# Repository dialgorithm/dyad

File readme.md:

<h1 align="center">
  dyad
  <br>
</h1>

<h4 align="center">
    esp32 + rp2040 dev board that's rpi zero sized
</h4>

## it features

- **ESP32-WROOM-32E** as the main controller
- **RP2040** as the secondary controller
- **micro sd** support
- **flash memory** for rp2040
- **dual** usb c, one for each mcu

## design

### 3d

| front                             | back                       |
| --------------------------------- | -------------------------- |
|  |  |

### overview

| schematic                          | pcb                    |
| ---------------------------------- | ---------------------- |
|  |  |

### layered pcb routes

| top layer                        | first layer                   |
| -------------------------------- | ----------------------------- |
|  |  |

| second layer                        | bottom layer                  |
| ----------------------------------- | ----------------------------- |
|  |  |

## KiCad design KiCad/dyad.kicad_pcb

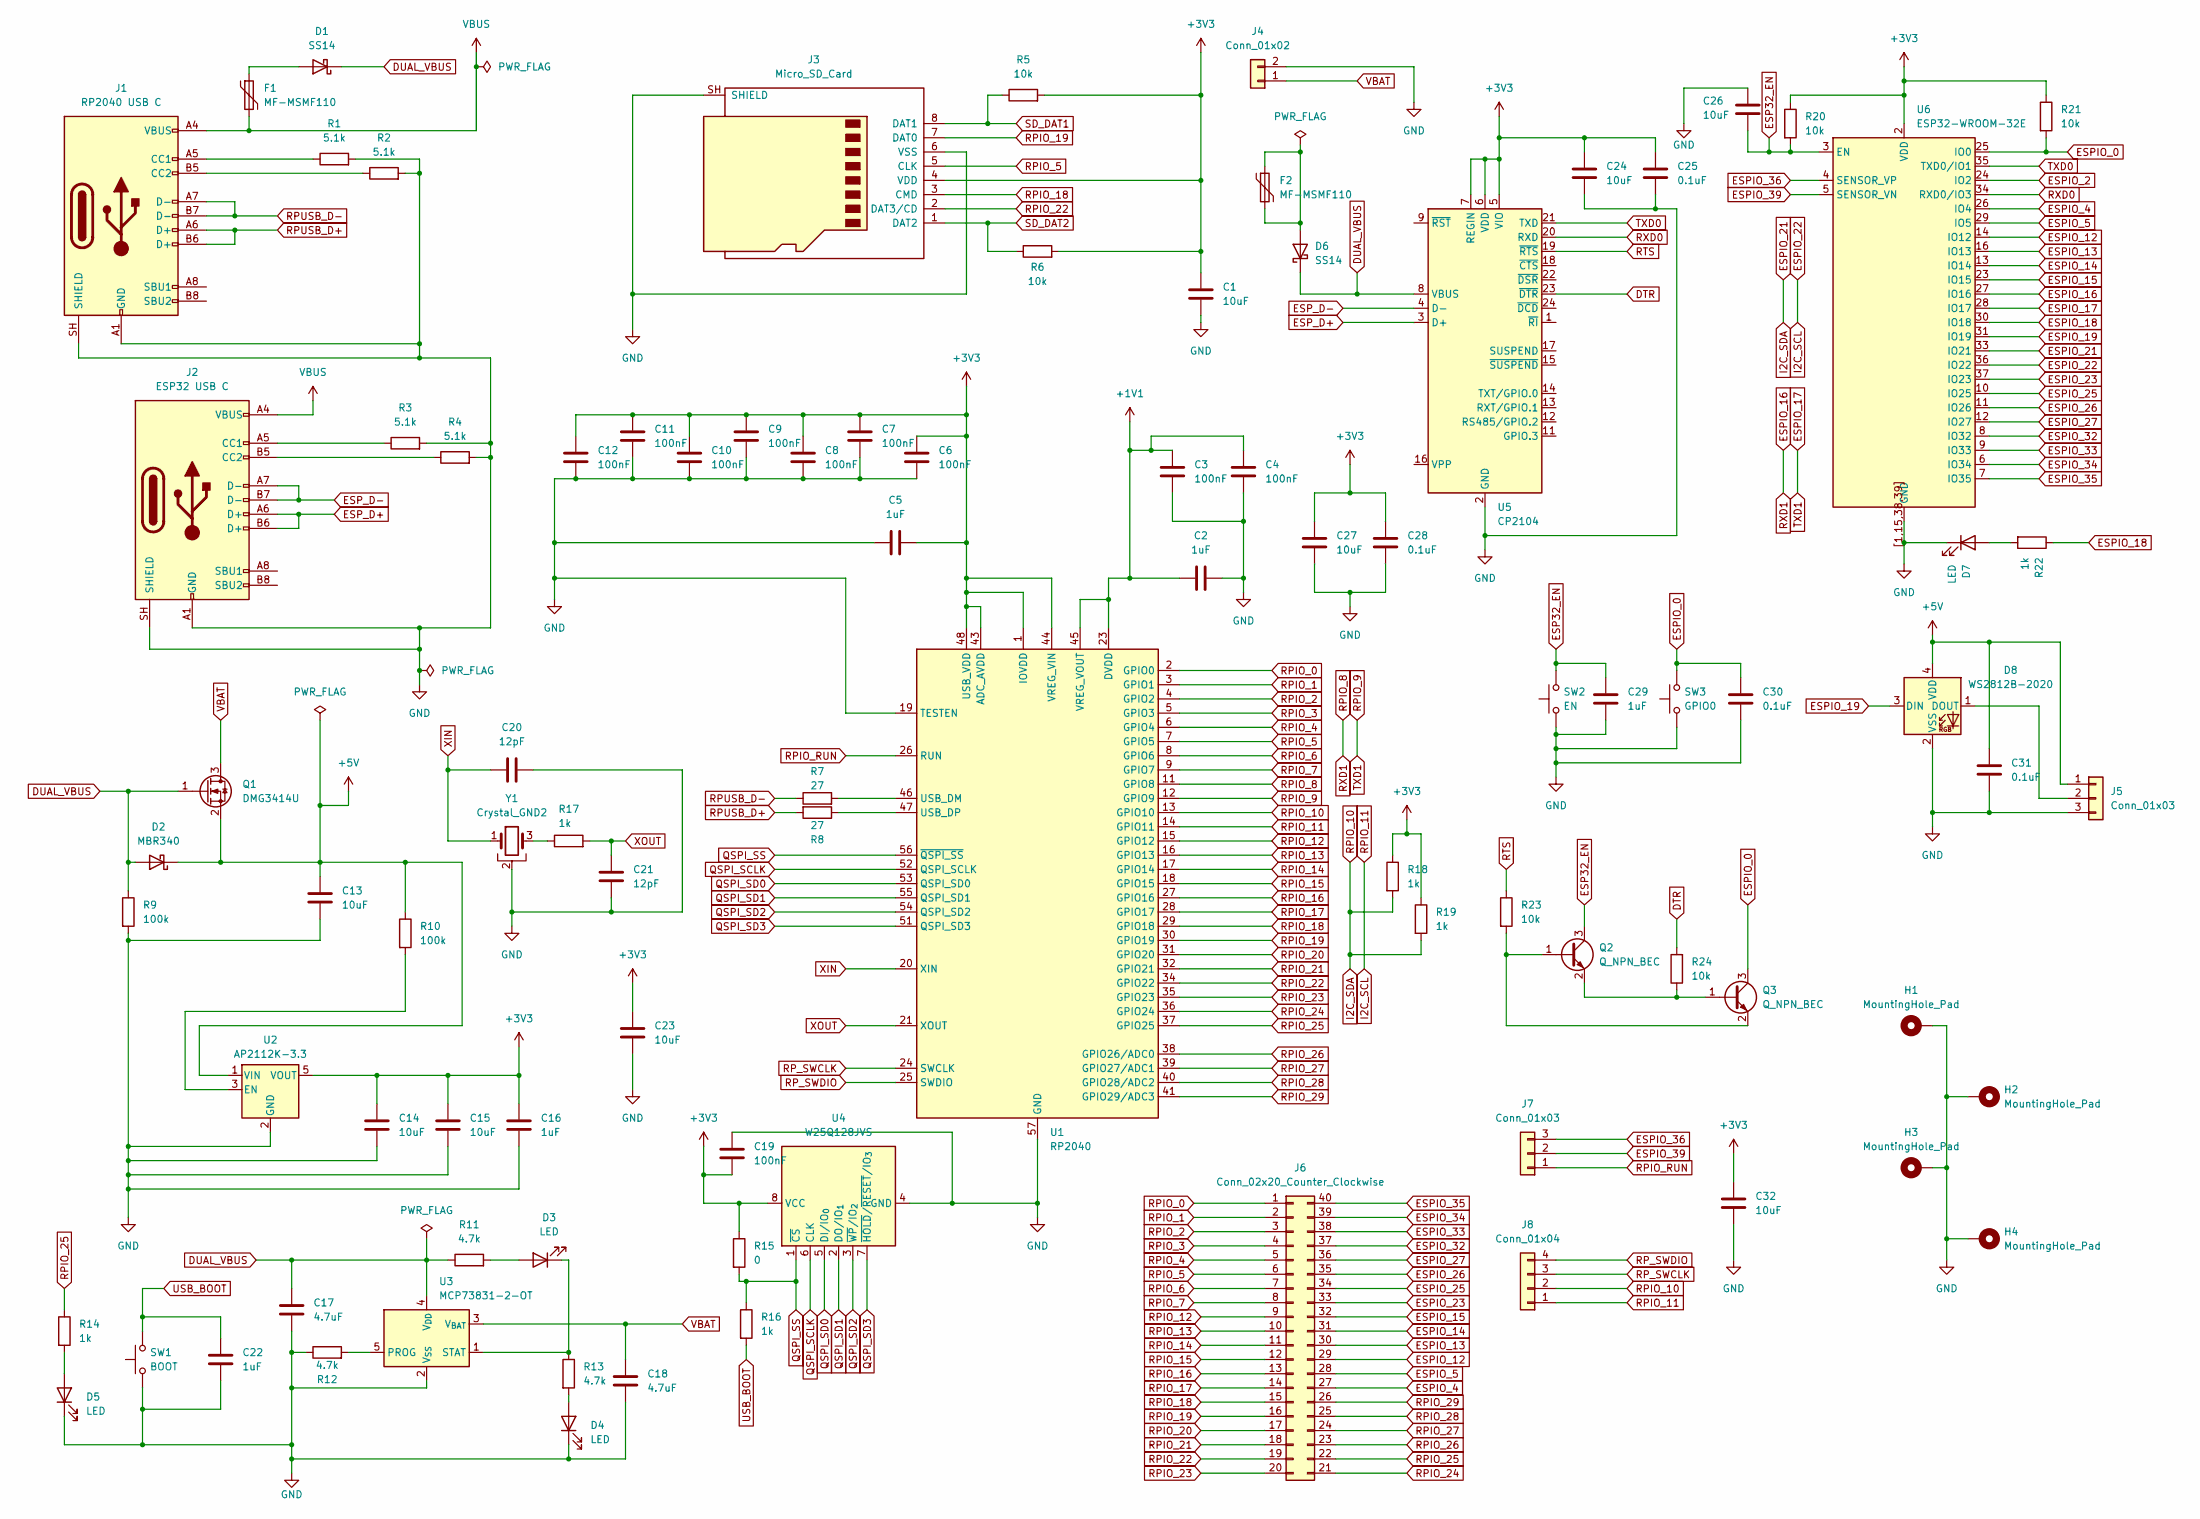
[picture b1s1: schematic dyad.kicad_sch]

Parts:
C1, C13, C14, C15, C23, C24, C26, C27, C32: 10uF; C_0603_1608Metric_Pad1.08x0.95mm_HandSolder
C2, C5, C16, C22, C29: 1uF; C_0603_1608Metric_Pad1.08x0.95mm_HandSolder
C3, C4, C6, C7, C8, C9, C10, C11, C12, C19: 100nF; C_0603_1608Metric_Pad1.08x0.95mm_HandSolder
C17, C18: 4.7uF; C_0603_1608Metric_Pad1.08x0.95mm_HandSolder
C20, C21: 12pF; C_0603_1608Metric_Pad1.08x0.95mm_HandSolder
C25, C28, C30, C31: 0.1uF; C_0603_1608Metric_Pad1.08x0.95mm_HandSolder
D1, D6: SS14; D_SMA
D2: MBR340; D_DO-201AD_P15.24mm_Horizontal
D3, D4, D5, D7: LED; LED_0603_1608Metric_Pad1.05x0.95mm_HandSolder
D8: WS2812B-2020; LED_WS2812B-2020_PLCC4_2.0x2.0mm
F1, F2: MF-MSMF110; Fuse_1206_3216Metric_Pad1.42x1.75mm_HandSolder
H1, H2, H3, H4: MountingHole_Pad; MountingHole_2.7mm_M2.5_DIN965_Pad
J1: RP2040 USB C; USB_C_Receptacle_HRO_TYPE-C-31-M-12
J2: ESP32 USB C; USB_C_Receptacle_HRO_TYPE-C-31-M-12
J3: Micro_SD_Card; microSD_HC_Hirose_DM3AT-SF-PEJM5
J4: Conn_01x02; JST_PH_B2B-PH-K_1x02_P2.00mm_Vertical
J5, J7: Conn_01x03; JST_PH_B3B-PH-K_1x03_P2.00mm_Vertical
J6: Conn_02x20_Counter_Clockwise; PinHeader_2x20_P2.54mm_Vertical
J8: Conn_01x04; JST_PH_B4B-PH-K_1x04_P2.00mm_Vertical
Q1: DMG3414U; SOT-23
Q2, Q3: Q_NPN_BEC; SOT-23
R1, R2, R3, R4: 5.1k; R_0603_1608Metric_Pad0.98x0.95mm_HandSolder
R5, R6, R20, R21, R23, R24: 10k; R_0603_1608Metric_Pad0.98x0.95mm_HandSolder
R7, R8: 27; R_0603_1608Metric_Pad0.98x0.95mm_HandSolder
R9, R10: 100k; R_0603_1608Metric_Pad0.98x0.95mm_HandSolder
R11, R12, R13: 4.7k; R_0603_1608Metric_Pad0.98x0.95mm_HandSolder
R14, R16, R17, R18, R19, R22: 1k; R_0603_1608Metric_Pad0.98x0.95mm_HandSolder
R15: 0; R_0603_1608Metric_Pad0.98x0.95mm_HandSolder
SW1: BOOT; SW_SPST_B3U-1000P
SW2: EN; SW_SPST_B3U-1000P
SW3: GPIO0; SW_SPST_B3U-1000P
U1: RP2040; QFN-56-1EP_7x7mm_P0.4mm_EP3.2x3.2mm
U2: AP2112K-3.3; SOT-23-5
U3: MCP73831-2-OT; SOT-23-5
U4: W25Q128JVS; SOIC-8_5.3x5.3mm_P1.27mm
U5: CP2104; QFN-24-1EP_4x4mm_P0.5mm_EP2.6x2.6mm
U6: ESP32-WROOM-32E
Y1: Crystal_GND2; Crystal_SMD_3225-4Pin_3.2x2.5mm_HandSoldering

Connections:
+1V1: C2.1, C3.1, C4.1, U1.23 (DVDD), U1.45 (VREG_VOUT), U1.50 (DVDD)
+3V3: C1.1, C5.2, C6.2, C7.2, C8.2, C9.2, C10.2, C11.2, C12.2, C14.1, C15.1, C16.1, C19.1, C23.1, C24.1, C25.1, C27.1, C28.1, C32.1, J3.4 (VDD), R5.2, R6.2, R15.1, R18.1, R19.1, R20.1, R21.1, U1.1 (IOVDD), U1.10 (IOVDD), U1.22 (IOVDD), U1.33 (IOVDD), U1.42 (IOVDD), U1.43 (ADC_AVDD), U1.44 (VREG_VIN), U1.48 (USB_VDD), U1.49 (IOVDD), U2.5 (VOUT), U4.8 (VCC), U5.5 (VIO), U5.6 (VDD), U5.7 (REGIN), U6.2 (VDD)
+5V: C13.1, C31.1, D2.1 (K), D8.4 (VDD), J5.1, Q1.2 (S), R10.1, U2.1 (VIN)
DTR: R24.2, U5.23 (~DTR)
DUAL_VBUS: C17.1, D1.1 (K), D2.2 (A), D6.1 (K), Q1.1 (G), R9.1, R11.1, U3.4 (V_{DD}), U5.8 (VBUS)
ESP32_EN: C26.2, C29.1, Q2.3 (C), R20.2, SW2.2, U6.3 (EN)
ESPIO_0: C30.1, Q3.3 (C), R21.2, SW3.2, U6.25 (IO0)
ESPIO_2: U6.24 (IO2)
ESPIO_4: J6.27, U6.26 (IO4)
ESPIO_5: J6.28, U6.29 (IO5)
ESPIO_12: J6.29, U6.14 (IO12)
ESPIO_13: J6.30, U6.16 (IO13)
ESPIO_14: J6.31, U6.13 (IO14)
ESPIO_15: J6.32, U6.23 (IO15)
ESPIO_16: U1.11 (GPIO8), U6.27 (IO16)
ESPIO_17: U1.12 (GPIO9), U6.28 (IO17)
ESPIO_18: R22.1, U6.30 (IO18)
ESPIO_19: D8.3 (DIN), U6.31 (IO19)
ESPIO_21: J8.2, R18.2, R19.2, U1.13 (GPIO10), U6.33 (IO21)
ESPIO_22: J8.1, U1.14 (GPIO11), U6.36 (IO22)
ESPIO_23: J6.33, U6.37 (IO23)
ESPIO_25: J6.34, U6.10 (IO25)
ESPIO_26: J6.35, U6.11 (IO26)
ESPIO_27: J6.36, U6.12 (IO27)
ESPIO_32: J6.37, U6.8 (IO32)
ESPIO_33: J6.38, U6.9 (IO33)
ESPIO_34: J6.39, U6.6 (IO34)
ESPIO_35: J6.40, U6.7 (IO35)
ESPIO_36: J7.3, U6.4 (SENSOR_VP)
ESPIO_39: J7.2, U6.5 (SENSOR_VN)
ESP_D+: J2.A6 (D+), J2.B6 (D+), U5.3 (D+)
ESP_D-: J2.A7 (D-), J2.B7 (D-), U5.4 (D-)
GND: C1.2, C2.2, C3.2, C4.2, C5.1, C6.1, C7.1, C8.1, C9.1, C10.1, C11.1, C12.1, C13.2, C14.2, C15.2, C16.2, C17.2, C18.2, C19.2, C20.2, C21.1, C22.2, C23.2, C24.2, C25.2, C26.1, C27.2, C28.2, C29.2, C30.2, C31.2, C32.2, D4.1 (K), D5.1 (K), D7.1 (K), D8.2 (VSS), H1.1 (1_1), H2.1 (1_1), H3.1 (1_1), H4.1 (1_1), J1.A1 (GND), J1.A12 (GND), J1.B1 (GND), J1.B12 (GND), J1.SH (SHIELD), J2.A1 (GND), J2.A12 (GND), J2.B1 (GND), J2.B12 (GND), J2.SH (SHIELD), J3.6 (VSS), J3.SH (SHIELD), J4.2, J5.3, R1.2, R2.2, R3.2, R4.2, R9.2, R12.1, SW1.1, SW2.1, SW3.1, U1.19 (TESTEN), U1.57 (GND), U2.2 (GND), U3.2 (V_{SS}), U4.4 (GND), U5.2 (GND), U5.25 (GND), U6.1 (GND), U6.15 (GND), U6.38 (GND), U6.39 (GND), U6.[1,15,38,39] (GND), Y1.2
unnamed: D1.2 (A), F1.1
unnamed: D3.2 (A), R11.2
unnamed: D3.1 (K), R13.1, U3.1 (STAT)
unnamed: D4.2 (A), R13.2
unnamed: D5.2 (A), R14.2
unnamed: D6.2 (A), F2.1, F2.2
unnamed: D7.2 (A), R22.2
unnamed: D8.1 (DOUT), J5.2
unnamed: J1.A5 (CC1), R1.1
unnamed: J1.B5 (CC2), R2.1
unnamed: J2.A5 (CC1), R3.1
unnamed: J2.B5 (CC2), R4.1
unnamed: Q2.1 (B), Q3.2 (E), R23.2
unnamed: Q2.2 (E), Q3.1 (B), R24.1
unnamed: R17.1, Y1.3
unnamed: R7.2, U1.46 (USB_DM)
unnamed: R8.1, U1.47 (USB_DP)
unnamed: R10.2, U2.3 (EN)
unnamed: R12.2, U3.5 (PROG)
QSPI_SCLK: U1.52 (QSPI_SCLK), U4.6 (CLK)
QSPI_SD0: U1.53 (QSPI_SD0), U4.5 (DI/IO_{0})
QSPI_SD1: U1.55 (QSPI_SD1), U4.2 (DO/IO_{1})
QSPI_SD2: U1.54 (QSPI_SD2), U4.3 (~WP/IO_{2})
QSPI_SD3: U1.51 (QSPI_SD3), U4.7 (~HOLD/~RESET/IO_{3})
QSPI_SS: R15.2, R16.1, U1.56 (~QSPI_SS), U4.1 (~CS)
RPIO_0: J6.1, U1.2 (GPIO0)
RPIO_1: J6.2, U1.3 (GPIO1)
RPIO_2: J6.3, U1.4 (GPIO2)
RPIO_3: J6.4, U1.5 (GPIO3)
RPIO_4: J6.5, U1.6 (GPIO4)
RPIO_5: J3.5 (CLK), J6.6, U1.7 (GPIO5)
RPIO_6: J6.7, U1.8 (GPIO6)
RPIO_7: J6.8, U1.9 (GPIO7)
RPIO_12: J6.9, U1.15 (GPIO12)
RPIO_13: J6.10, U1.16 (GPIO13)
RPIO_14: J6.11, U1.17 (GPIO14)
RPIO_15: J6.12, U1.18 (GPIO15)
RPIO_16: J6.13, U1.27 (GPIO16)
RPIO_17: J6.14, U1.28 (GPIO17)
RPIO_18: J3.3 (CMD), J6.15, U1.29 (GPIO18)
RPIO_19: J3.7 (DAT0), J6.16, U1.30 (GPIO19)
RPIO_20: J6.17, U1.31 (GPIO20)
RPIO_21: J6.18, U1.32 (GPIO21)
RPIO_22: J3.2 (DAT3/CD), J6.19, U1.34 (GPIO22)
RPIO_23: J6.20, U1.35 (GPIO23)
RPIO_24: J6.21, U1.36 (GPIO24)
RPIO_25: J6.22, R14.1, U1.37 (GPIO25)
RPIO_26: J6.23, U1.38 (GPIO26/ADC0)
RPIO_27: J6.24, U1.39 (GPIO27/ADC1)
RPIO_28: J6.25, U1.40 (GPIO28/ADC2)
RPIO_29: J6.26, U1.41 (GPIO29/ADC3)
RPIO_RUN: J7.1, U1.26 (RUN)
RPUSB_D+: J1.A6 (D+), J1.B6 (D+), R8.2
RPUSB_D-: J1.A7 (D-), J1.B7 (D-), R7.1
RP_SWCLK: J8.3, U1.24 (SWCLK)
RP_SWDIO: J8.4, U1.25 (SWDIO)
RTS: R23.1, U5.19 (~RTS)
RXD0: U5.20 (RXD), U6.34 (RXD0/IO3)
SD_DAT1: J3.8 (DAT1), R5.1
SD_DAT2: J3.1 (DAT2), R6.1
TXD0: U5.21 (TXD), U6.35 (TXD0/IO1)
USB_BOOT: C22.1, R16.2, SW1.2
VBAT: C18.1, J4.1, Q1.3 (D), U3.3 (V_{BAT})
VBUS: F1.2, J1.A4 (VBUS), J1.A9 (VBUS), J1.B4 (VBUS), J1.B9 (VBUS), J2.A4 (VBUS), J2.A9 (VBUS), J2.B4 (VBUS), J2.B9 (VBUS)
XIN: C20.1, U1.20 (XIN), Y1.1
XOUT: C21.2, R17.2, U1.21 (XOUT)

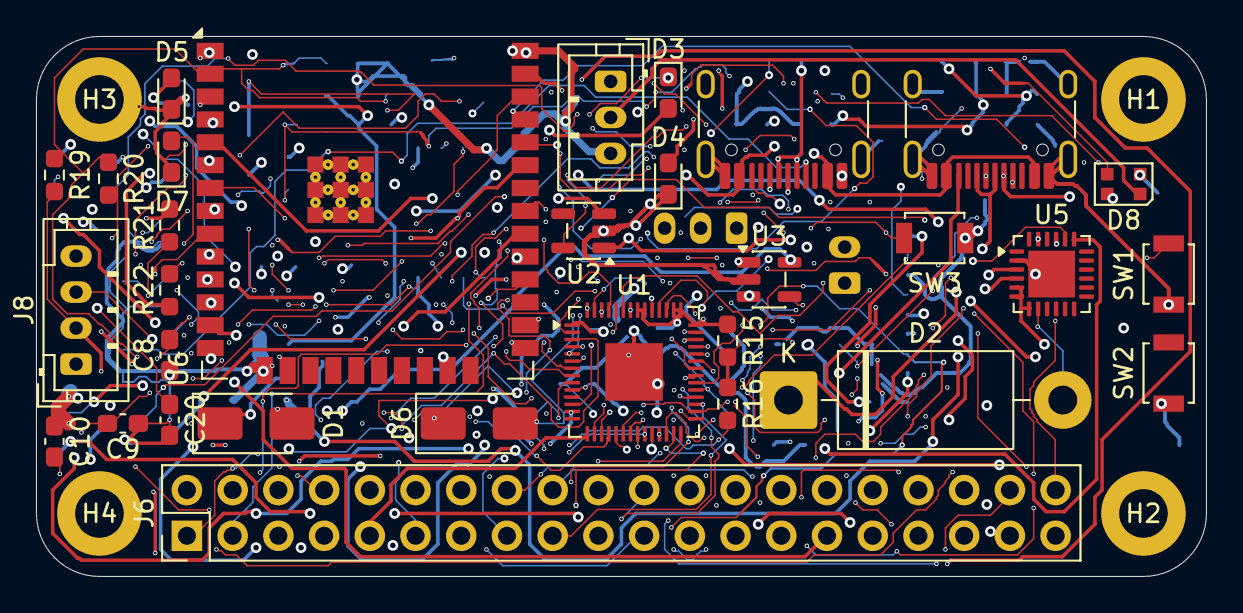
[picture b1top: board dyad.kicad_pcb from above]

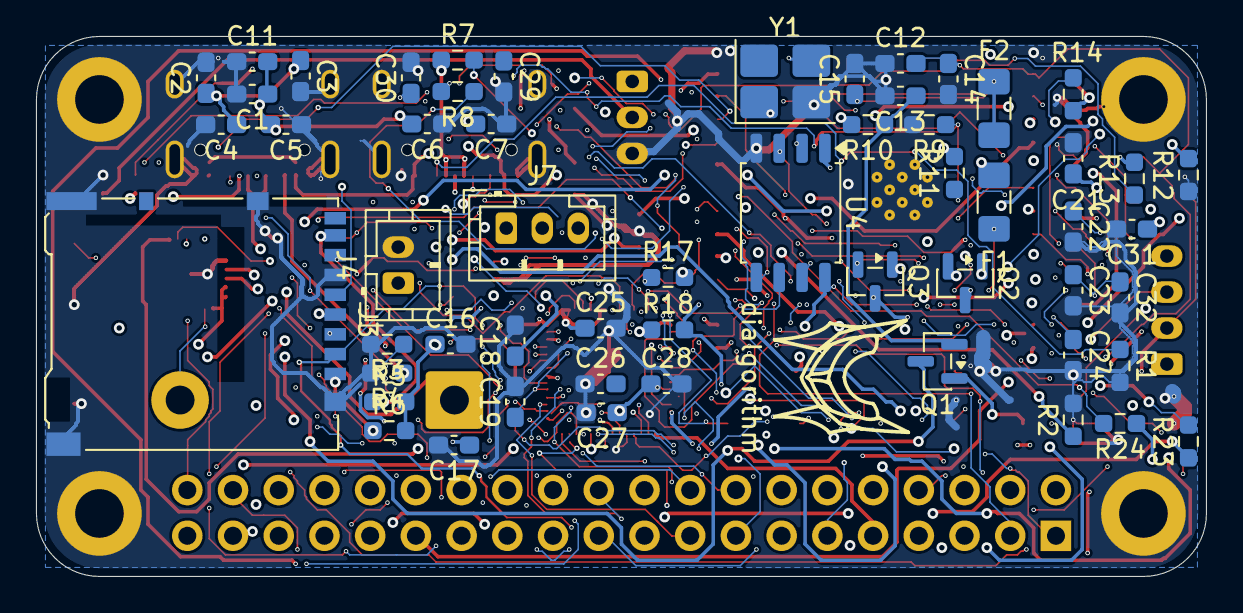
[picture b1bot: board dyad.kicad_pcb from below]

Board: 4 copper layers, 65.0 x 30.0 mm, 92 parts (57 on the bottom side), 98 nets.

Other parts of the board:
dialgorithm: dialgorithm
